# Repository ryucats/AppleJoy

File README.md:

# AppleJoy
Adapter for Atari/Sega joysticks on Apple ][ / Franklin ACE 1000

This is a slight reworking of Tor Arne Hustvedt's "Apple IIe digital joystick adaptor for using Kempston/Atari/Amiga digital joysticks on an Apple IIe", available at https://www.pcbway.com/project/shareproject/Apple_IIe_digital_joystick_adaptor_for_using_Kempston_SEGA_Atari_Amiga_digital_joysticks_on_an_Apple_IIe.html

The schematic has been recreated from the board file, and the BC558 PNP transistors have been replaced with 2N3906 transistors (which seem to be more readily available).

STL files for a 3d-printed case are in the stl/ directory.

The resulting board works perfectly on a Franklin ACE 1000 using an Apple //e-to-][+ game port adapter purchased from console5 (https://console5.com/store/byteboosters-9-pin-to-dip-16-pin-joystick-adapter-for-apple-ii-plus.html).  As it appears to be out of stock, I'll trace out the connections at some point and publish a DIY clone.

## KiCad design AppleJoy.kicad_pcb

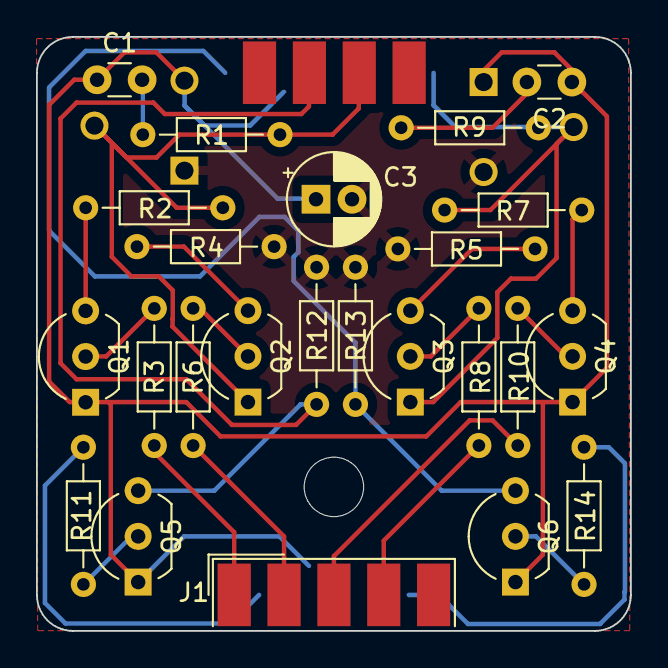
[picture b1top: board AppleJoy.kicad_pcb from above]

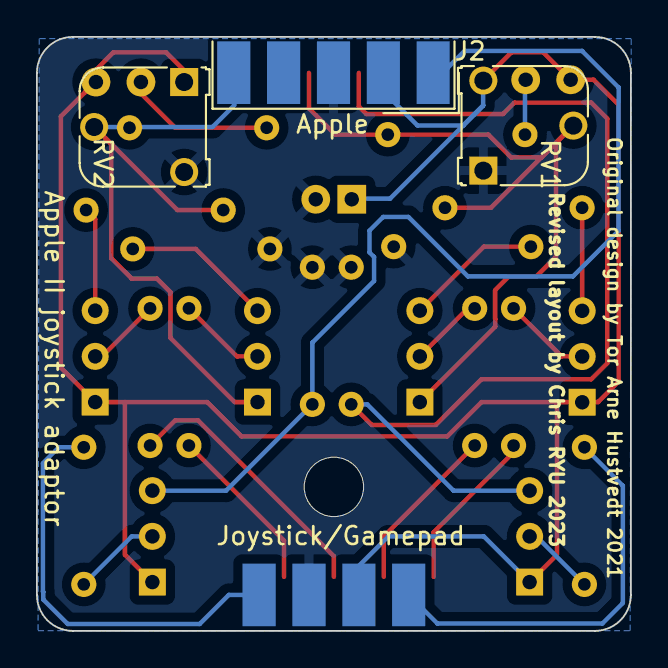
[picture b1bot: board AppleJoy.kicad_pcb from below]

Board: 2 copper layers, 33.0 x 33.0 mm, 27 parts (3 on the bottom side), 24 nets.

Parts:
C1, C2: C_Small; C_Disc_D3.0mm_W1.6mm_P2.50mm
C3: 1uF; CP_Radial_D5.0mm_P2.00mm
J1: Atari; DSUB-9_Male_EdgeMount_P2.77mm
J2: Apple; DSUB-9_Male_EdgeMount_P2.77mm
Q1, Q2, Q3, Q4, Q5, Q6: BC558; TO-92_Inline_Wide
R1, R2, R3, R6, R7, R8, R9, R10, R11, R14: 1k; R_Axial_DIN0204_L3.6mm_D1.6mm_P7.62mm_Horizontal
R4, R5: 10k; R_Axial_DIN0204_L3.6mm_D1.6mm_P7.62mm_Horizontal
R12, R13: 560; R_Axial_DIN0204_L3.6mm_D1.6mm_P7.62mm_Horizontal
RV1, RV2: 100k; Potentiometer_Runtron_RM-065_Vertical

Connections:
+5V: C1.1, C2.1, C3.1, J1.7, J2.2, Q1.1 (E), Q4.1 (E), Q5.1 (E), Q6.1 (E), RV1.3, RV2.1
BUT_0: J2.7, Q5.3 (C), R12.2
BUT_1: J2.1, Q6.3 (C), R13.2
DOWN: J1.2, R6.2
GAME0: J2.5, Q3.1 (E), R7.1, R9.2, RV2.2
GAME1: J2.8, Q2.1 (E), R1.2, R2.1, RV1.2
GND: C3.2, J1.8, J2.3, R4.1, R5.1, R12.1, R13.1, RV1.1, RV2.3
LEFT: J1.3, R10.2
unnamed: C1.2, R1.1
unnamed: C2.2, R9.1
unnamed: Q1.2 (B), R3.1
unnamed: Q1.3 (C), R2.2
unnamed: Q2.2 (B), R6.1
unnamed: Q2.3 (C), R4.2
unnamed: Q3.2 (B), R8.1
unnamed: Q3.3 (C), R5.2
unnamed: Q4.2 (B), R10.1
unnamed: Q4.3 (C), R7.2
unnamed: Q5.2 (B), R11.1
unnamed: Q6.2 (B), R14.1
PADDLE_A: J1.9, R14.2
RIGHT: J1.4, R8.2
TRIGGER: J1.6, R11.2
UP: J1.1, R3.2

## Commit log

2023-04-07 Initial commit.
2023-04-07 Add description.
2023-04-07 Add note about STL files.
2023-04-07 Add the KiCAD files.
2023-04-09 Spelling.
2023-04-10 Slight tweaks for PCBway.
